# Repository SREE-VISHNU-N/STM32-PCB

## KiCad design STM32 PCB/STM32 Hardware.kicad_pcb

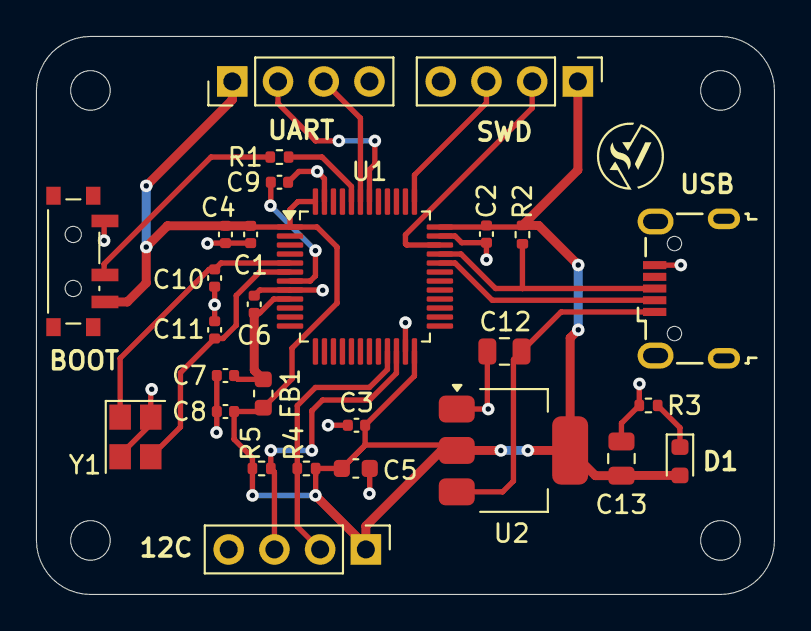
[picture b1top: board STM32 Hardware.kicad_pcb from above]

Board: 2 copper layers, 41.0 x 31.0 mm, 32 parts (0 on the bottom side), 18 nets.

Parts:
12C: Conn_01x04_Pin; PinHeader_1x04_P2.54mm_Vertical
BOOT: SW_SPDT; SW_SPDT_PCM12_V2
C1, C2, C3, C4, C9: 100n; C_0402_1005Metric
C5: 10u; C_0603_1608Metric
C6: 10n; C_0402_1005Metric
C7, C8: 1u; C_0402_1005Metric
C10, C11: 10p; C_0402_1005Metric
C12, C13: 22u; C_0805_2012Metric
D1: RED; LED_0603_1608Metric
FB1: 120R; L_0603_1608Metric
H1, H2, H3, H4: MountingHole; MountingHole_2.2mm_M2
R1: 10k; R_0402_1005Metric
R2, R3, R4, R5: 1k5; R_0402_1005Metric
SWD: Conn_01x04_Pin; PinHeader_1x04_P2.54mm_Vertical
U1: STM32F103C8T6; LQFP-48_7x7mm_P0.5mm
U2: AMS1117-3.3; SOT-223-3_TabPin2
UART: Conn_01x04_Pin; PinHeader_1x04_P2.54mm_Vertical
USB: USB_B_Micro; USB_Micro-B_Wuerth_629105150521
Y1: 16MHz; Crystal_SMD_3225-4Pin_3.2x2.5mm

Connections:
+3.3V: 12C.1, BOOT.3 (C), C1.1, C2.1, C3.1, C4.1, C5.1, C8.1, C13.1, D1.2 (A), FB1.2, R2.1, R4.1, R5.1, SWD.1, U1.1 (VBAT), U1.24 (VDD), U1.36 (VDD), U1.48 (VDD), U2.2 (VO), UART.1
+3.3VA: C6.1, C7.1, FB1.1, U1.9 (VDDA)
/BOOT0: R1.2, U1.44 (BOOT0)
/HSE_IN: C10.1, U1.5 (PD0), Y1.1
/HSE_OUT: C11.1, U1.6 (PD1), Y1.3
/I2C2_SCL: 12C.2, R4.2, U1.21 (PB10)
/I2C2_SDA: 12C.3, R5.2, U1.22 (PB11)
/NRST: C9.1, U1.7 (NRST)
/PWR_LED_K: D1.1 (K), R3.1
/SWCLK: SWD.3, U1.37 (PA14)
/SWDIO: SWD.2, U1.34 (PA13)
/SW_BOOT0: BOOT.2 (B), R1.1
/USART1_RX: U1.43 (PB7), UART.3
/USART1_TX: U1.42 (PB6), UART.2
/USB_D+: R2.2, U1.33 (PA12), USB.3 (D+)
/USB_D-: U1.32 (PA11), USB.2 (D-)
GND: 12C.4, BOOT.1 (A), C1.2, C2.2, C3.2, C4.2, C5.2, C6.2, C7.2, C8.2, C9.2, C10.2, C11.2, C12.2, C13.2, R3.2, SWD.4, U1.8 (VSSA), U1.23 (VSS), U1.35 (VSS), U1.47 (VSS), U2.1 (GND), UART.4, USB.5 (GND), Y1.2, Y1.4
VBUS: C12.1, U2.3 (VI), USB.1 (VBUS)

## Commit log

2025-01-17 Create stm
2025-01-17 Create F
2025-01-17 Create G
2025-01-17 Add files via upload
    USB 3D Graphic
